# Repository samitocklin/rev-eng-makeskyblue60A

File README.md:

# Reverse engineering the MakeSkyBlue 60A MPPT

KiCad reverse-engineering of the MakeSkyBlue 60A MPPT solar charge controller, plus replacement ESP32 firmware for units with a dead NUC029 MCU.

## Schematic

| Power stage | Aux flyback supply |
|---|---|
|  |  |
| **PV input switch, shunt, terminals** | **MCU (NUC029LAN), buttons, LCD** |
|  |  |

To regenerate the images: `python3 tools/export_sch_images.py`

## Layout

| Path | Contents |
|---|---|
| `MakeSkyBlue-60A.kicad_*` | Schematic and PCB (KiCad 10) |
| `*.kicad_sym` + `sym-lib-table` | Project symbols: NUC029LAN, NUC120VE3DN, RS8551, TLP350, HY1920W |
| `Datasheets/` | Local only (git-ignored); download links in [`Datasheets/SOURCES.md`](Datasheets/SOURCES.md) |
| `replacement_esp32_firmware/` | ESP-IDF firmware for ESP32-C5-Zero + ST7789 TFT ([README](replacement_esp32_firmware/README.md)) |
| `tools/` | Python scripts that generate symbols, footprints and images |
| `pictures/` | Board photo, schematic images |

## Hardware notes

- **Power stage:** 4× HY1920W N-MOSFETs (200 V/90 A, TO-247) and 4× STTH3003 diodes, driven by TLP350 gate-drive optos.
- **Mounting:** every TO-220/TO-247 part sits on the back side, lying flat with the tab facing the heatsink. The footprints are `*_Horizontal_TabUp`; flip them to B.Cu in the PCB.
- **Aux supply:** UC3845 flyback through TR1 (custom transformer marked `MP-1248-3MF1554`; the symbol is a placeholder). It feeds the +15 V gate-driver rail, plus +12 V and +5 V.

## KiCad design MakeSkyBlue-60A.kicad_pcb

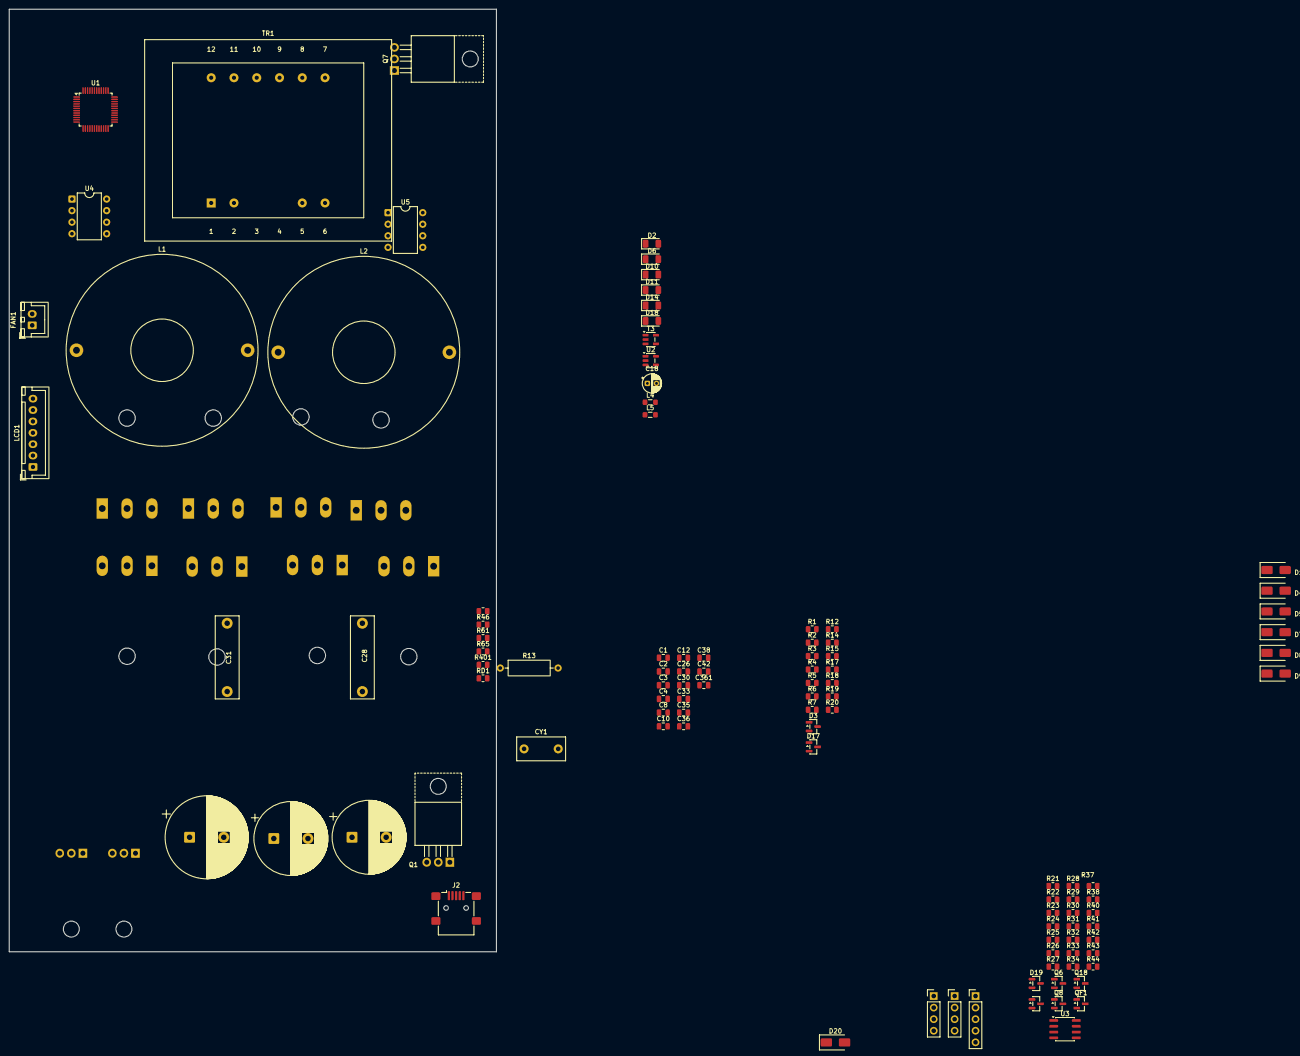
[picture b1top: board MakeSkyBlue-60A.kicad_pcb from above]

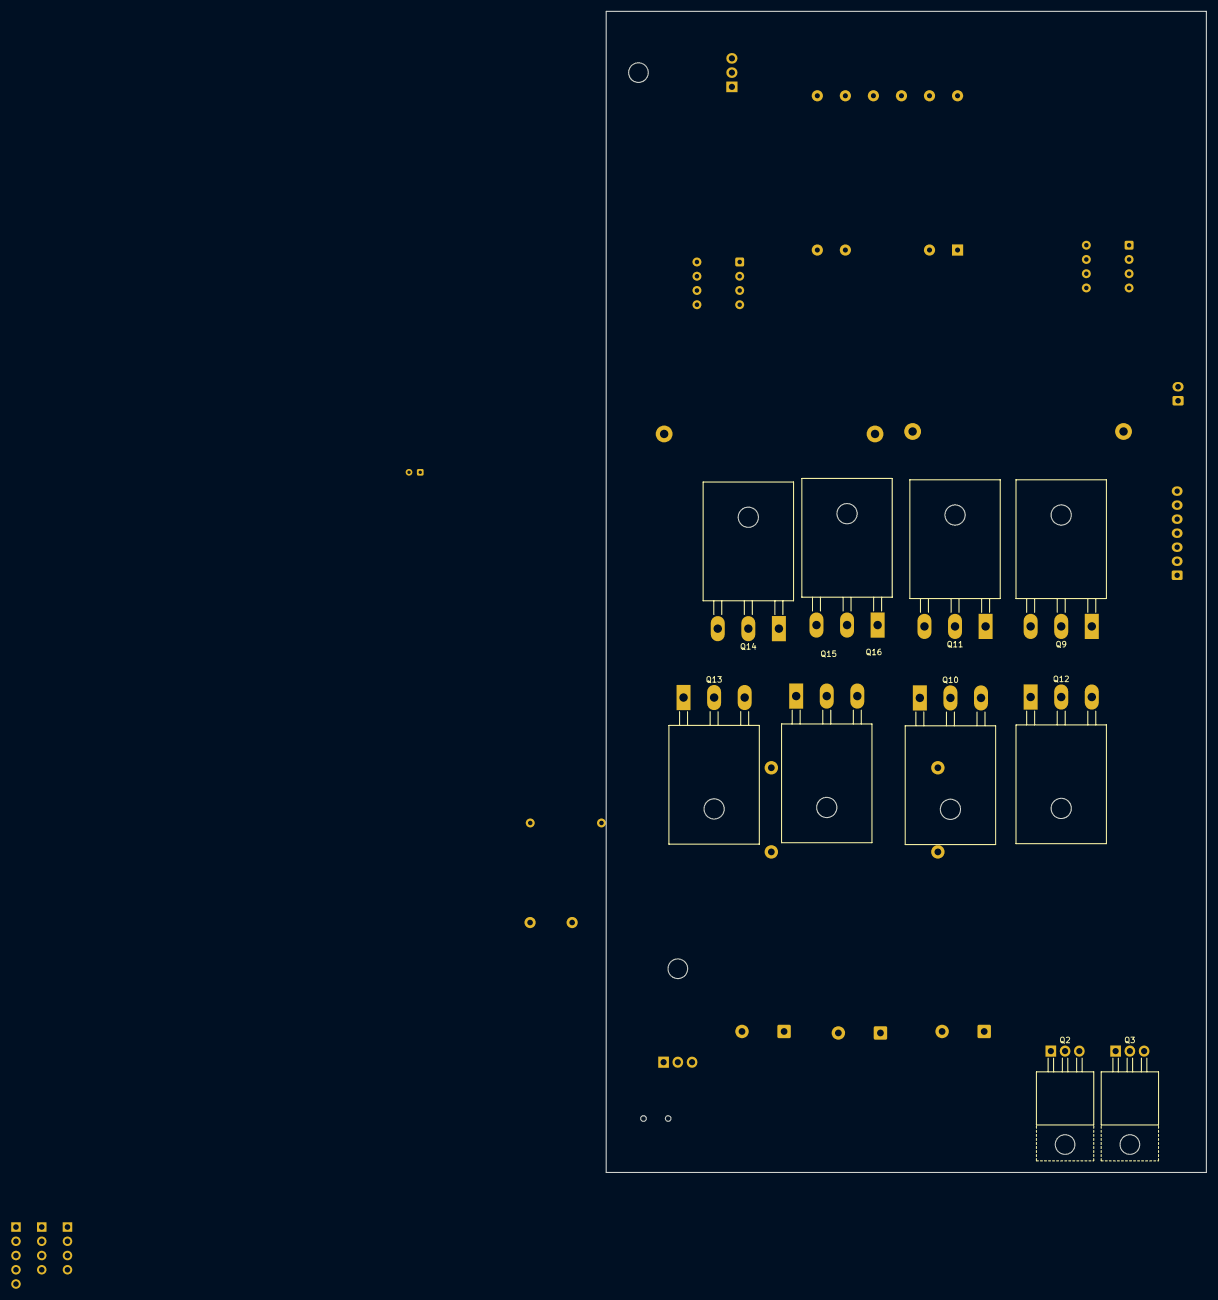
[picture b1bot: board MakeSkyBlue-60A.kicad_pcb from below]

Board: 2 copper layers, 107.0 x 207.0 mm, 114 parts (10 on the bottom side), 72 nets, no tracks yet.

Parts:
C1, C8, C10, C26, C33, C38, C42, C361: C; C_0805_2012Metric
C2: 150nF; C_0805_2012Metric
C3: 1,9uF; C_0805_2012Metric
C4, C12, C30: 1uF; C_0805_2012Metric
C18: 16V 47uF; CP_Radial_D4.0mm_P2.00mm
C23, C27: 470uF 100V; CP_Radial_D16.0mm_P7.50mm
C25: 470uF 200V; CP_Radial_D18.0mm_P7.50mm
C28, C31: 1uF 400V; C_Rect_L18.0mm_W5.0mm_P15.00mm_FKS3_FKP3
C35, C36: -; C_0805_2012Metric
CY1: 10nF; C_Disc_D10.5mm_W5.0mm_P7.50mm
D1, D8, D9: US2MA; D_SMA
D2, D6, D10, D11, D14, D18: D; D_1206_3216Metric
D3, D17, D19: BAV99; SOT-23
D4, D5, D7, D20: US1M; D_SMA
FAN1: JST XH B2; JST_XH_B2B-XH-A_1x02_P2.50mm_Vertical
J2: USB_B_Mini; USB_Mini-B_Lumberg_2486_01_Horizontal
JP2: Buttons; PinHeader_1x05_P2.54mm_Vertical
JP5, JP6: UART; PinHeader_1x04_P2.54mm_Vertical
L1, L2: 150uH 0.2ohm; L_Toroid_Horizontal_D41.9mm_P37.60mm_Vishay_TJ7
L4, L5: L; L_0805_2012Metric_Pad1.05x1.20mm_HandSolder
LCD1: Screen; JST_XH_B7B-XH-A_1x07_P2.50mm_Vertical
Q1: IRF540N; TO-220-3_Horizontal_TabUp
Q2, Q3: PMOS; TO-220-3_Horizontal_TabUp
Q5, Q8, Q18: MMBT3904; SOT-23
Q6: MMBT3906; SOT-23
Q7: IRF640N; TO-220-3_Horizontal_TabUp
Q9, Q11, Q14, Q16: STTH3003; TO-247-3_Horizontal_TabUp
Q10, Q12, Q13, Q15: HY1920W; TO-247-3_Horizontal_TabUp
QF1: SS8050; SOT-23
R1: 100k; R_0805_2012Metric
R2, R6, R15, R18, R23, R25, R26, R28, R30, R37, R38, R40, R45, R46, R401: 10k; R_0805_2012Metric
R3: R_Shunt; R_0805_2012Metric
R4, R20, R44: 2.4k; R_0805_2012Metric
R5: 4.2k; R_0805_2012Metric
R7: 120k; R_0805_2012Metric
R12, R14, R17, R21: 10R; R_0805_2012Metric
R13: R?; R_Axial_DIN0309_L9.0mm_D3.2mm_P12.70mm_Horizontal
R19, R34, R42, R61: 4.7k; R_0805_2012Metric
R22, R24, R27, R33: 22R; R_0805_2012Metric
R29: 1k; R_0805_2012Metric
R31, R32: 470R; R_0805_2012Metric
R41, R43: 150k; R_0805_2012Metric
R65: 100R; R_0805_2012Metric
RD1: 10k; R_0805_2012Metric
T3: RS8551XF; SOT-23-5
TR1: MP-1248-3MF1554; Transformer_Breve_TEZ-44x52
U1: NUC029LAN; LQFP-48_7x7mm_P0.5mm
U2: MIC5205-5.0YM5; SOT-23-5
U3: UC3845_SOIC8; SOIC-8_3.9x4.9mm_P1.27mm
U4, U5: TLP350; DIP-8_W7.62mm

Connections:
+3V3: C33.1, L4.1, LCD1.7, U1.41 (VDD), U1.42 (AVDD)
+5V: C30.1, D17.2 (A), D19.2 (A), JP6.4, R12.2, R28.2, R29.1, R37.1, U2.5 (OUT)
+12V: C12.1, D8.1 (K), FAN1.2, Q6.2 (E), R15.1, R45.2
+15V: C18.1, C35.2, C36.2, D7.1 (K), R38.2, R40.2, U4.8 (VCC), U5.8 (VCC)
+BATT: C23.1, C27.1, D20.1 (K), L1.2, L2.2, R41.2
+PV: C2.2, D3.1 (K), D18.2 (A), Q2.3 (S), Q3.3 (S), R1.1, R43.2
/CONV1_PWM: R31.1, U1.19 (P2.0)
/CONV2_PWM: R32.1, U1.21 (P2.2)
/FAN_PWM: R34.1, U1.29 (P4.5)
/LOAD_EN: R46.2, R61.1, U1.28 (P4.4)
/LOAD_G_DRV: Q1.1 (G), Q18.3 (C), R45.1
/PV_DRIVE: R18.2, R20.1, U1.23 (P2.4)
/PV_SHUNT_POS: R3.2, R4.2
/PV_SHUNT_SIG: R19.1, U1.43 (P1.0)
/RX: JP6.3, U1.37 (P0.3)
/TX: JP6.2, U1.38 (P0.2)
/V_SENS_BAT: D17.3 (K), R41.1, R42.2, U1.47 (P1.4)
/V_SENS_PV: D19.3 (K), R43.1, R44.2, U1.46 (P1.3)
GND: C12.2, C23.2, C25.2, C27.2, C28.2, C31.2, C33.2, C38.2, C42.1, CY1.1, D17.1 (K), D19.1 (K), JP2.1, JP6.1, LCD1.6, Q1.2 (D), Q5.2 (E), Q8.2 (E), Q9.1 (A1), Q9.3 (A2), Q11.1 (A1), Q11.3 (A2), Q14.1 (A1), Q14.3 (A2), Q16.1 (A1), Q16.3 (A2), Q18.2 (E), QF1.2 (E), R3.1, R13.2, R20.2, R42.1, R44.1, RD1.1, T3.2 (V-), T3.3 (+), TR1.5, U1.6 (AVSS), U1.17 (VSS), U2.2 (GND), U3.5 (GND), U4.3 (K), U5.3 (K)
GND1: C18.2, C35.1, C36.1, R38.1, R40.1, TR1.10, U4.5 (GND), U5.5 (GND)
unnamed: C3.1, D3.3 (K)
unnamed: C8.2, R7.1, R19.2, T3.1
unnamed: C26.1, L5.2
unnamed: C361.1, R401.2, TR1.2
unnamed: D1.2 (A), R2.1
unnamed: C1.2, D1.1 (K), R6.1, TR1.1
unnamed: D2.1 (K), R2.2, U3.7 (VCC)
unnamed: C2.1, D3.2 (A), R1.2, R65.1
unnamed: D4.2 (A), Q7.2 (D)
unnamed: C1.1, D4.1 (K), R6.2
unnamed: D5.2 (A), R17.2
unnamed: C361.2, D5.1 (K), R401.1
unnamed: D6.2 (A), Q10.1 (G), R22.2, R23.1
unnamed: D7.2 (A), R21.1
unnamed: D8.2 (A), TR1.8
unnamed: D9.2 (A), TR1.6, TR1.7
unnamed: D9.1 (K), U2.1 (IN), U2.3 (EN)
unnamed: D10.2 (A), Q12.1 (G), R24.2, R25.1
unnamed: D6.1 (K), D10.1 (K), R22.1, R24.1, U4.6 (VO)
unnamed: D11.2 (A), Q13.1 (G), R26.1, R27.2
unnamed: D11.1 (K), D14.1 (K), R27.1, R33.1, U5.6 (VO)
unnamed: D14.2 (A), Q15.1 (G), R30.1, R33.2
unnamed: D18.1 (K), Q2.2 (G), Q3.2 (G), R65.2
unnamed: D20.2 (A), Q1.3 (S)
unnamed: FAN1.1, QF1.3 (C)
unnamed: JP2.2, U1.10 (P3.4)
unnamed: JP2.3, U1.11 (P3.5)
unnamed: JP2.4, U1.9 (P3.3)
unnamed: JP2.5, U1.8 (P3.2)
unnamed: L4.2, R61.2
unnamed: L5.1, R29.2
unnamed: LCD1.1, U1.36 (P4.1)
unnamed: LCD1.3, U1.35 (P0.4)
unnamed: LCD1.4, U1.34 (P0.5)
unnamed: LCD1.5, U1.33 (P0.6)
unnamed: Q5.1 (B), Q6.1 (B), Q8.3 (C), R15.2
unnamed: C4.2, Q5.3 (C), Q6.3 (C)
unnamed: Q7.1 (G), R14.2, RD1.2
unnamed: Q7.3 (S), R13.1
unnamed: Q8.1 (B), R18.1
unnamed: C25.1, C28.1, C31.1, Q2.1 (D), Q3.1 (D), Q10.2 (D), Q12.2 (D), Q13.2 (D), Q15.2 (D), R23.2, R25.2, R26.2, R30.2
unnamed: L1.1, Q9.2 (K), Q10.3 (S), Q11.2 (K), Q12.3 (S)
unnamed: L2.1, Q13.3 (S), Q14.2 (K), Q15.3 (S), Q16.2 (K)
unnamed: Q18.1 (B), R46.1
unnamed: QF1.1 (B), R34.2
unnamed: R21.2, TR1.9
unnamed: C8.1, R4.1, R7.2, T3.4 (-)
unnamed: C30.2, U2.4 (BP)
unnamed: R14.1, U3.6 (OUT)
unnamed: R5.2, U3.4 (RC)
unnamed: R31.2, U4.2 (A)
unnamed: R32.2, U5.2 (A)
